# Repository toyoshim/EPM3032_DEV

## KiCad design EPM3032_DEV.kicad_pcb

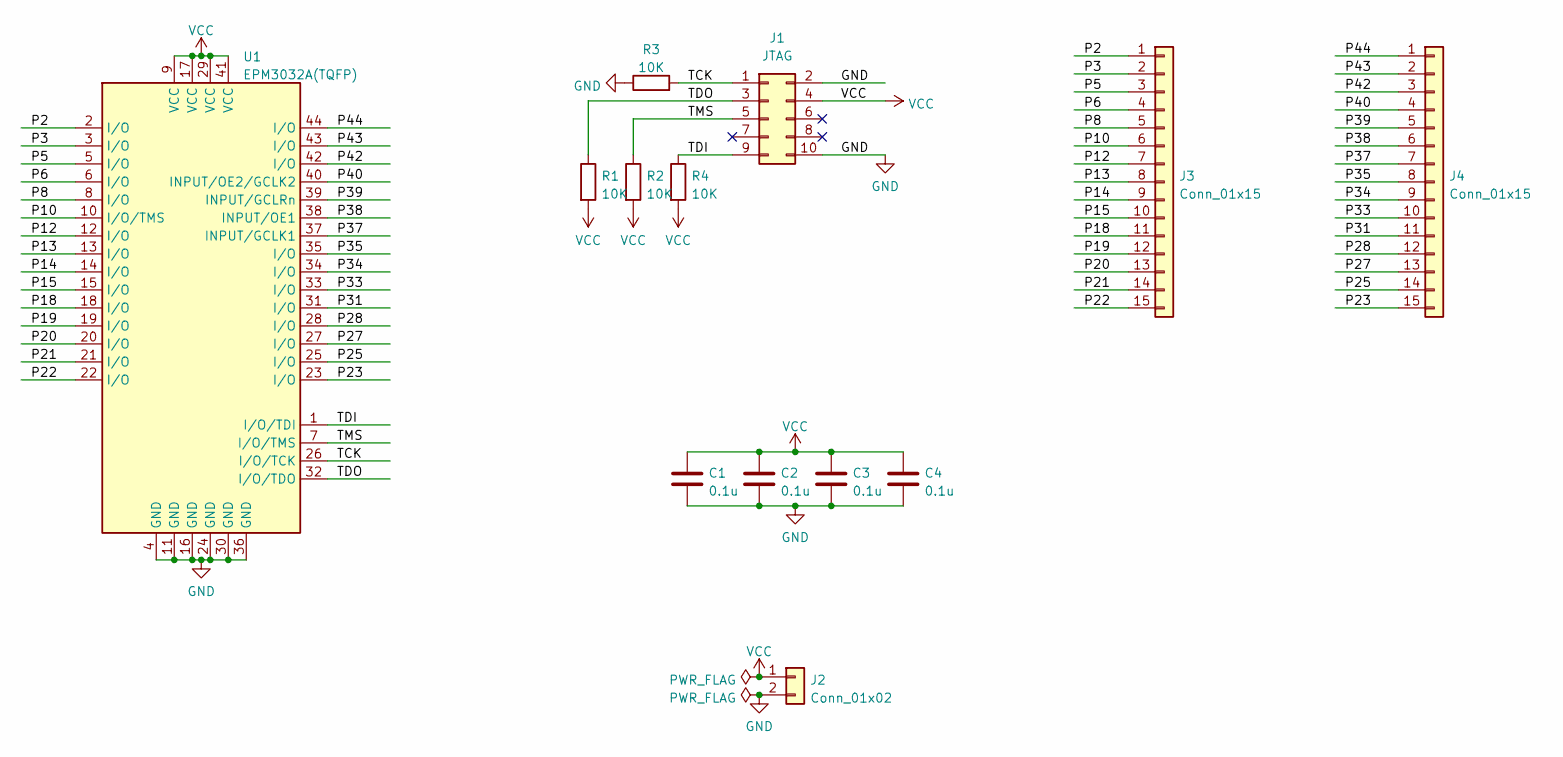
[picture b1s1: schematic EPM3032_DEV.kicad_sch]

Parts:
C1, C2, C3, C4: 0.1u; C_0603_1608Metric_Pad1.08x0.95mm_HandSolder
J1: JTAG; PinHeader_2x05_P2.54mm_Vertical
J2: Conn_01x02; PinHeader_1x02_P2.54mm_Vertical
J3, J4: Conn_01x15; PinHeader_1x15_P2.54mm_Vertical
R1, R2, R3, R4: 10K; R_0603_1608Metric_Pad0.98x0.95mm_HandSolder
U1: EPM3032A(TQFP); TQFP-44_10x10mm_P0.8mm

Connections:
/P2: J3.1, U1.2 (I/O)
/P3: J3.2, U1.3 (I/O)
/P5: J3.3, U1.5 (I/O)
/P6: J3.4, U1.6 (I/O)
/P8: J3.5, U1.8 (I/O)
/P10: J3.6, U1.10 (I/O/TMS)
/P12: J3.7, U1.12 (I/O)
/P13: J3.8, U1.13 (I/O)
/P14: J3.9, U1.14 (I/O)
/P15: J3.10, U1.15 (I/O)
/P18: J3.11, U1.18 (I/O)
/P19: J3.12, U1.19 (I/O)
/P20: J3.13, U1.20 (I/O)
/P21: J3.14, U1.21 (I/O)
/P22: J3.15, U1.22 (I/O)
/P23: J4.15, U1.23 (I/O)
/P25: J4.14, U1.25 (I/O)
/P27: J4.13, U1.27 (I/O)
/P28: J4.12, U1.28 (I/O)
/P31: J4.11, U1.31 (I/O)
/P33: J4.10, U1.33 (I/O)
/P34: J4.9, U1.34 (I/O)
/P35: J4.8, U1.35 (I/O)
/P37: J4.7, U1.37 (INPUT/GCLK1)
/P38: J4.6, U1.38 (INPUT/OE1)
/P39: J4.5, U1.39 (INPUT/GCLRn)
/P40: J4.4, U1.40 (INPUT/OE2/GCLK2)
/P42: J4.3, U1.42 (I/O)
/P43: J4.2, U1.43 (I/O)
/P44: J4.1, U1.44 (I/O)
/TCK: J1.1, R3.2, U1.26 (I/O/TCK)
/TDI: J1.9, R4.1, U1.1 (I/O/TDI)
/TDO: J1.3, R1.1, U1.32 (I/O/TDO)
/TMS: J1.5, R2.1, U1.7 (I/O/TMS)
GND: C1.2, C2.2, C3.2, C4.2, J1.2, J1.10, J2.2, R3.1, U1.4 (GND), U1.11 (GND), U1.16 (GND), U1.24 (GND), U1.30 (GND), U1.36 (GND)
VCC: C1.1, C2.1, C3.1, C4.1, J1.4, J2.1, R1.2, R2.2, R4.2, U1.9 (VCC), U1.17 (VCC), U1.29 (VCC), U1.41 (VCC)

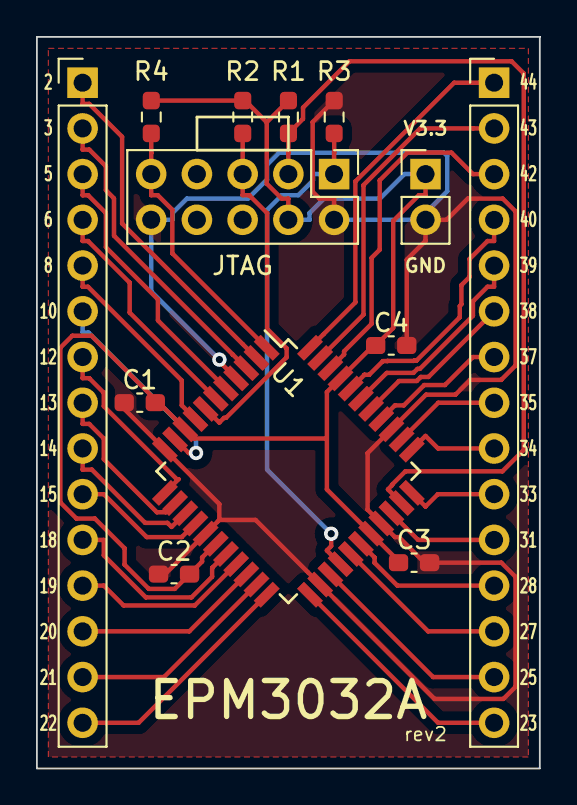
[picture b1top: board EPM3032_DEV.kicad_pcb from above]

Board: 2 copper layers, 27.9 x 40.6 mm, 13 parts (0 on the bottom side), 36 nets.

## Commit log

2022-10-09 Rev2
